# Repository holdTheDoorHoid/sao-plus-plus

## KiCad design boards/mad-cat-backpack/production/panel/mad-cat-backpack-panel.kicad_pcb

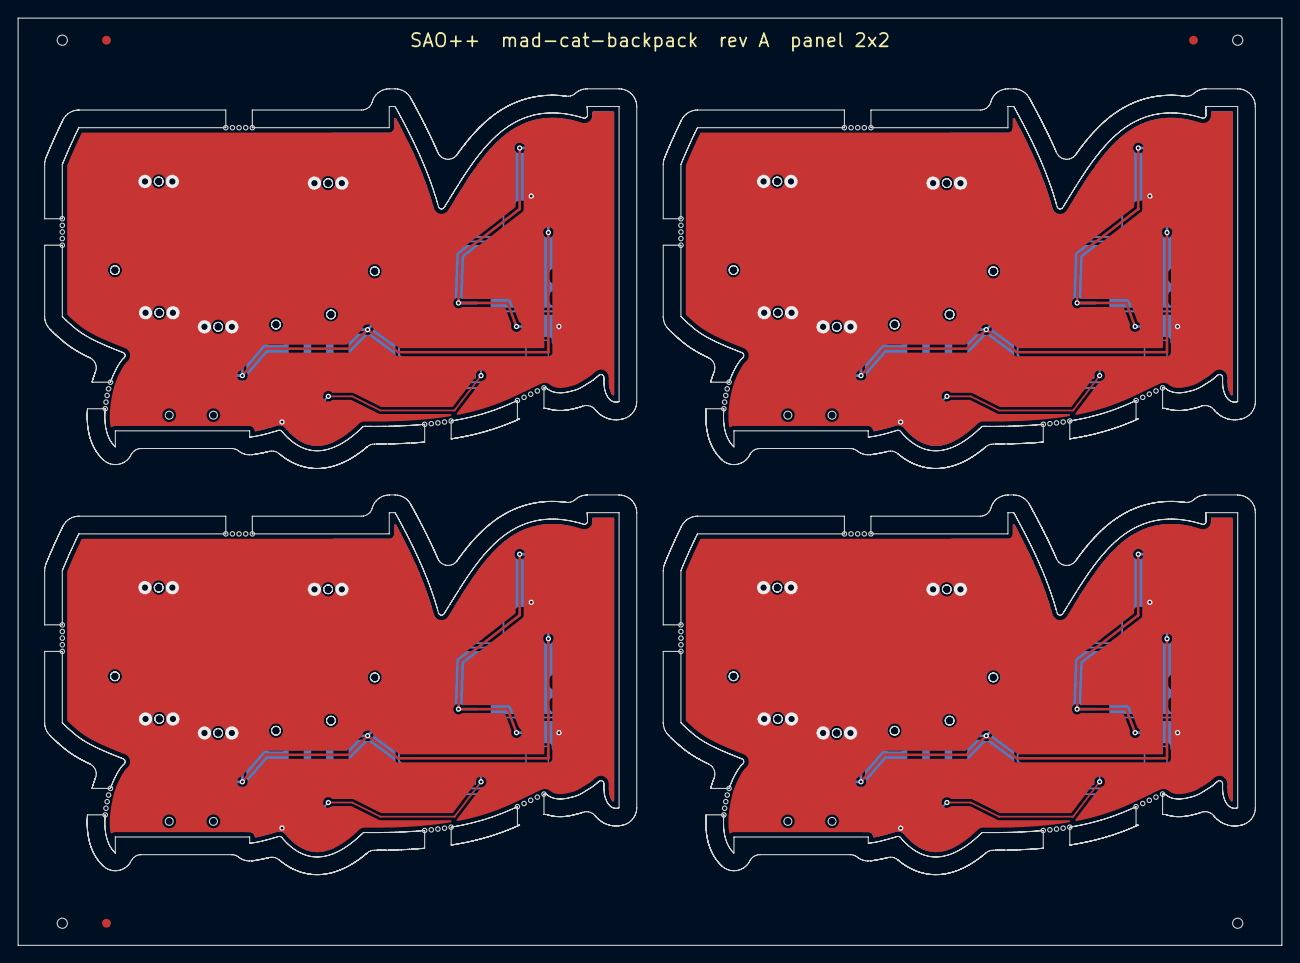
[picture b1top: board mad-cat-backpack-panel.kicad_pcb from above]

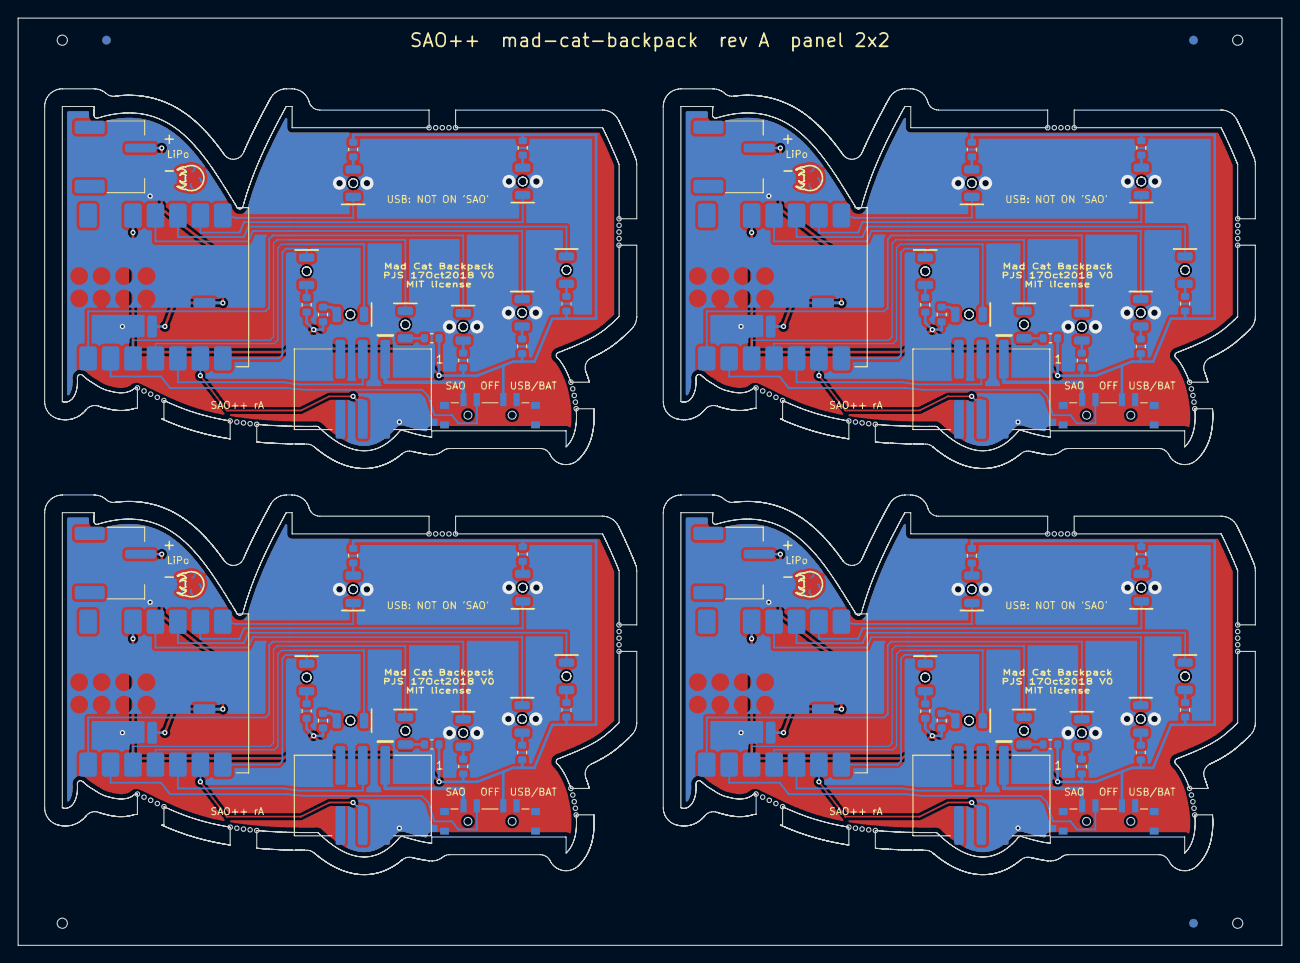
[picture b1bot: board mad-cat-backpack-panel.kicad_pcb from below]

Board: 2 copper layers, 143.0 x 104.9 mm, 80 parts (80 on the bottom side), 92 nets.

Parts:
D101, D102, D103, D104, D105, D106, D107, D108, D201, D202, D203, D204, D205, D206, D207, D208, D301, D302, D303, D304, D305, D306, D307, D308, D401, D402, D403, D404, D405, D406, D407, D408: white; SAOPP_LED-10_1206_ReverseMount_ThroughBoard
J101, J201, J301, J401: SAO v1.69bis; SAOPP_CONN-01_BoxHeader_2x03_P2.54mm_SMD_XFCN_BH254VS-6P
J102, J202, J302, J402: LiPo 3.7 V; SAOPP_CONN-10_JST_PH_S2B-PH-SM4-TB_1x02_Horizontal
R101, R102, R103, R104, R105, R106, R107, R108, R201, R202, R203, R204, R205, R206, R207, R208, R301, R302, R303, R304, R305, R306, R307, R308, R401, R402, R403, R404, R405, R406, R407, R408: 330; SAOPP_R_0603_1608Metric
SW101, SW201, SW301, SW401: SAO / OFF / BAT; SAOPP_SW-01_Slide_SP3T_CK_PCM13SMTR
U101, U201, U301, U401: XIAO ESP32-C3 / S3 / C6; SAOPP_MCU-01_Seeed_XIAO_SMD_C3_S3_C6

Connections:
B2-BAT+: J202.1, U201.15
B2-GND: J201.2, J202.2, U201.13, U201.16
B2-LED1_A: D201.2, R201.1
B2-LED1_K: D201.1, U201.9
B2-LED2_A: D202.2, R202.1
B2-LED2_K: D202.1, U201.8
B2-LED3_A: D203.2, R203.1
B2-LED3_K: D203.1, U201.10
B2-LED4_A: D204.2, R204.1
B2-LED4_K: D204.1, U201.11
B2-LED5_A: D205.2, R205.1
B2-LED5_K: D205.1, U201.1
B2-LED6_A: D206.2, R206.1
B2-LED6_K: D206.1, U201.3
B2-LED7_A: D207.2, R207.1
B2-LED7_K: D207.1, U201.4
B2-LED8_A: D208.2, R208.1
B2-LED8_K: D208.1, U201.7
B2-OFF_SENSE: SW201.2, U201.2
B2-SCL: J201.4, U201.6
B2-SDA: J201.3, U201.5
B2-V3V3: R201.2, R202.2, R203.2, R204.2, R205.2, R206.2, R207.2, R208.2, SW201.3, U201.12
B2-VSAO: J201.1, SW201.1
B3-BAT+: J302.1, U301.15
B3-GND: J301.2, J302.2, U301.13, U301.16
B3-LED1_A: D301.2, R301.1
B3-LED1_K: D301.1, U301.9
B3-LED2_A: D302.2, R302.1
B3-LED2_K: D302.1, U301.8
B3-LED3_A: D303.2, R303.1
B3-LED3_K: D303.1, U301.10
B3-LED4_A: D304.2, R304.1
B3-LED4_K: D304.1, U301.11
B3-LED5_A: D305.2, R305.1
B3-LED5_K: D305.1, U301.1
B3-LED6_A: D306.2, R306.1
B3-LED6_K: D306.1, U301.3
B3-LED7_A: D307.2, R307.1
B3-LED7_K: D307.1, U301.4
B3-LED8_A: D308.2, R308.1
B3-LED8_K: D308.1, U301.7
B3-OFF_SENSE: SW301.2, U301.2
B3-SCL: J301.4, U301.6
B3-SDA: J301.3, U301.5
B3-V3V3: R301.2, R302.2, R303.2, R304.2, R305.2, R306.2, R307.2, R308.2, SW301.3, U301.12
B3-VSAO: J301.1, SW301.1
B4-BAT+: J402.1, U401.15
B4-GND: J401.2, J402.2, U401.13, U401.16
B4-LED1_A: D401.2, R401.1
B4-LED1_K: D401.1, U401.9
B4-LED2_A: D402.2, R402.1
B4-LED2_K: D402.1, U401.8
B4-LED3_A: D403.2, R403.1
B4-LED3_K: D403.1, U401.10
B4-LED4_A: D404.2, R404.1
B4-LED4_K: D404.1, U401.11
B4-LED5_A: D405.2, R405.1
B4-LED5_K: D405.1, U401.1
B4-LED6_A: D406.2, R406.1
B4-LED6_K: D406.1, U401.3
B4-LED7_A: D407.2, R407.1
B4-LED7_K: D407.1, U401.4
B4-LED8_A: D408.2, R408.1
B4-LED8_K: D408.1, U401.7
B4-OFF_SENSE: SW401.2, U401.2
B4-SCL: J401.4, U401.6
B4-SDA: J401.3, U401.5
B4-V3V3: R401.2, R402.2, R403.2, R404.2, R405.2, R406.2, R407.2, R408.2, SW401.3, U401.12
B4-VSAO: J401.1, SW401.1
BAT+: J102.1, U101.15
GND: J101.2, J102.2, U101.13, U101.16
LED1_A: D101.2, R101.1
LED1_K: D101.1, U101.9
LED2_A: D102.2, R102.1
LED2_K: D102.1, U101.8
LED3_A: D103.2, R103.1
LED3_K: D103.1, U101.10
LED4_A: D104.2, R104.1
LED4_K: D104.1, U101.11
LED5_A: D105.2, R105.1
LED5_K: D105.1, U101.1
LED6_A: D106.2, R106.1
LED6_K: D106.1, U101.3
LED7_A: D107.2, R107.1
LED7_K: D107.1, U101.4
LED8_A: D108.2, R108.1
LED8_K: D108.1, U101.7
OFF_SENSE: SW101.2, U101.2
SCL: J101.4, U101.6
SDA: J101.3, U101.5
V3V3: R101.2, R102.2, R103.2, R104.2, R105.2, R106.2, R107.2, R108.2, SW101.3, U101.12
VSAO: J101.1, SW101.1

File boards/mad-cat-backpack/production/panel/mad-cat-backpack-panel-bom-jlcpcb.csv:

Comment,Designator,Footprint,LCSC Part #
white,"D101,D102,D103,D104,D105,D106,D107,D108,D201,D202,D203,D204,D205,D206,D207,D208,D301,D302,D303,D304,D305,D306,D307,D308,D401,D402,D403,D404,D405,D406,D407,D408",SAOPP_LED-10_1206_ReverseMount_ThroughBoard,C575513
SAO v1.69bis,"J101,J201,J301,J401",SAOPP_CONN-01_BoxHeader_2x03_P2.54mm_SMD_XFCN_BH254VS-6P,C492445
LiPo 3.7 V,"J102,J202,J302,J402",SAOPP_CONN-10_JST_PH_S2B-PH-SM4-TB_1x02_Horizontal,C295747
330,"R101,R102,R103,R104,R105,R106,R107,R108,R201,R202,R203,R204,R205,R206,R207,R208,R301,R302,R303,R304,R305,R306,R307,R308,R401,R402,R403,R404,R405,R406,R407,R408",SAOPP_R_0603_1608Metric,C23138
SAO / OFF / BAT,"SW101,SW201,SW301,SW401",SAOPP_SW-01_Slide_SP3T_CK_PCM13SMTR,C221842
XIAO ESP32-C3 / S3 / C6,"U101,U201,U301,U401",SAOPP_MCU-01_Seeed_XIAO_SMD_C3_S3_C6,

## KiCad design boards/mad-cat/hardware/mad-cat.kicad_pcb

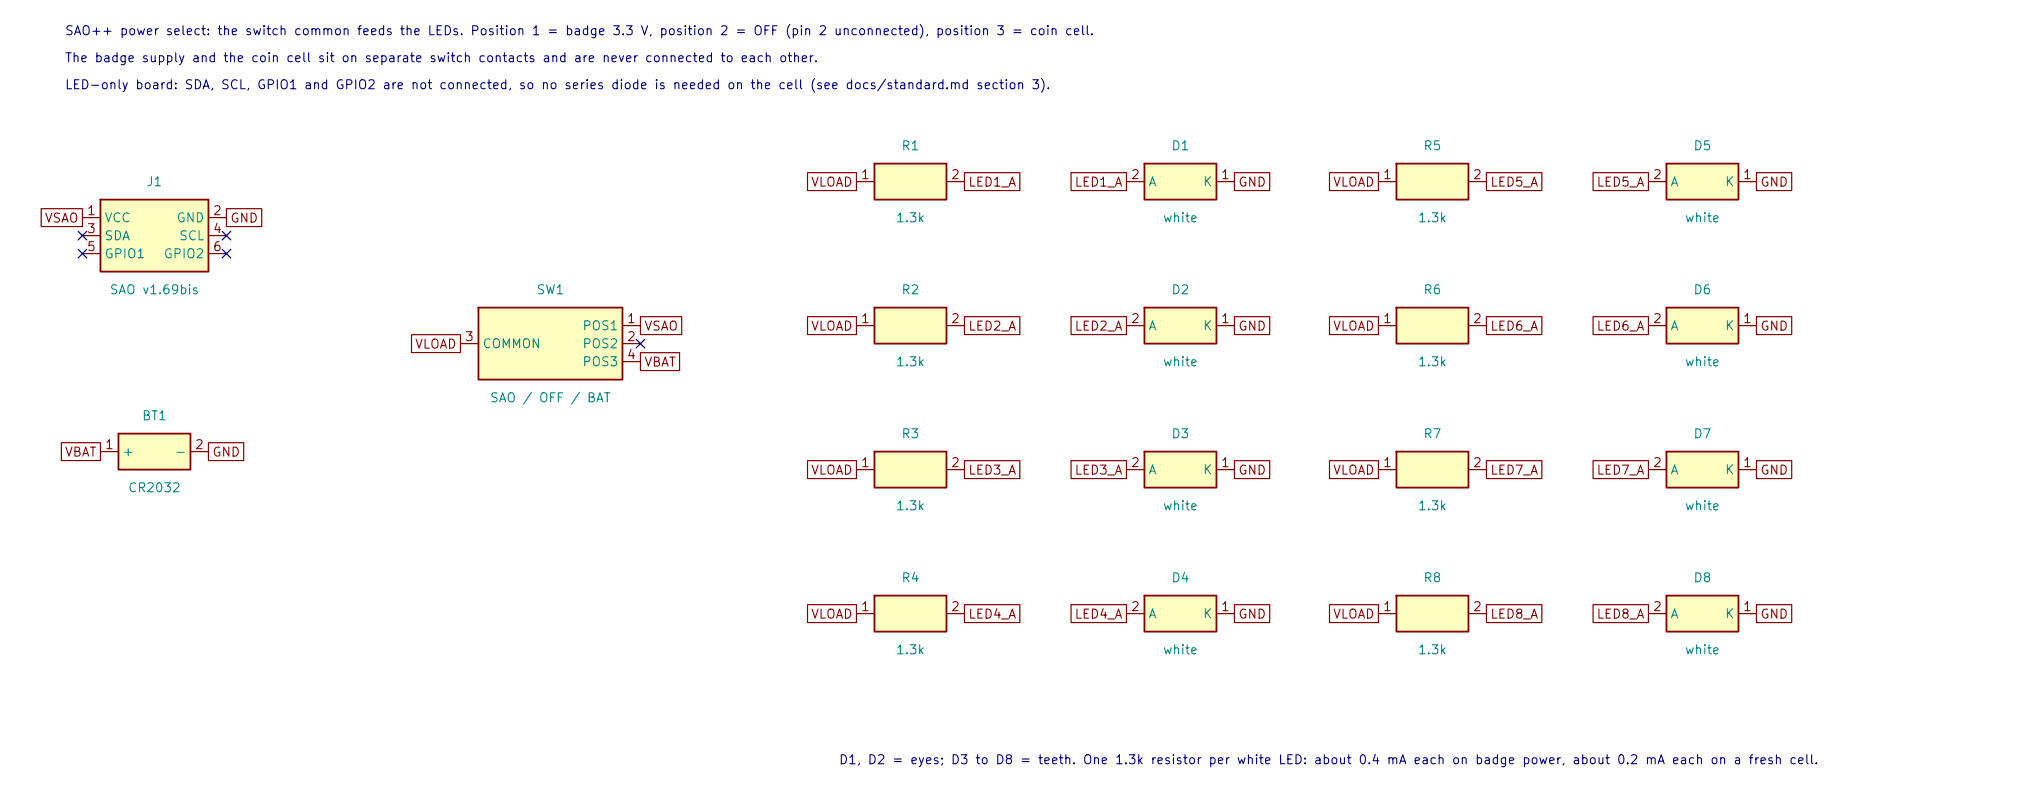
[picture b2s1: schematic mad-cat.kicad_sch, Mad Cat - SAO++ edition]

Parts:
BT1: CR2032; SAOPP_BAT-01_CR2032_SMD_TE_BAT-HLD-001; MPN BAT-HLD-001; LCSC C7501066
D1, D2, D3, D4, D5, D6, D7, D8: white; SAOPP_LED-10_1206_ReverseMount_ThroughBoard; MPN LTW-C230DS; LCSC C575513
J1: SAO v1.69bis; SAOPP_CONN-01_BoxHeader_2x03_P2.54mm_SMD_XFCN_BH254VS-6P; MPN BH254VS-6P; LCSC C492445
R1, R2, R3, R4, R5, R6, R7, R8: 1.3k; SAOPP_R_0603_1608Metric; MPN 0603WAF1301T5E; LCSC C22767
SW1: SAO / OFF / BAT; SAOPP_SW-01_Slide_SP3T_CK_PCM13SMTR; MPN PCM13SMTR; LCSC C221842

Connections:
GND: BT1.2 (-), D1.1 (K), D2.1 (K), D3.1 (K), D4.1 (K), D5.1 (K), D6.1 (K), D7.1 (K), D8.1 (K), J1.2 (GND)
LED1_A: D1.2 (A), R1.2
LED2_A: D2.2 (A), R2.2
LED3_A: D3.2 (A), R3.2
LED4_A: D4.2 (A), R4.2
LED5_A: D5.2 (A), R5.2
LED6_A: D6.2 (A), R6.2
LED7_A: D7.2 (A), R7.2
LED8_A: D8.2 (A), R8.2
VBAT: BT1.1 (+), SW1.4 (POS3)
VLOAD: R1.1, R2.1, R3.1, R4.1, R5.1, R6.1, R7.1, R8.1, SW1.3 (COMMON)
VSAO: J1.1 (VCC), SW1.1 (POS1)

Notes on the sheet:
SAO++ power select: the switch common feeds the LEDs. Position 1 = badge 3.3 V, position 2 = OFF (pin 2 unconnected), position 3 = coin cell.
The badge supply and the coin cell sit on separate switch contacts and are never connected to each other.
LED-only board: SDA, SCL, GPIO1 and GPIO2 are not connected, so no series diode is needed on the cell (see docs/standard.md section 3).
D1, D2 = eyes; D3 to D8 = teeth. One 1.3k resistor per white LED: about 0.4 mA each on badge power, about 0.2 mA each on a fresh cell.

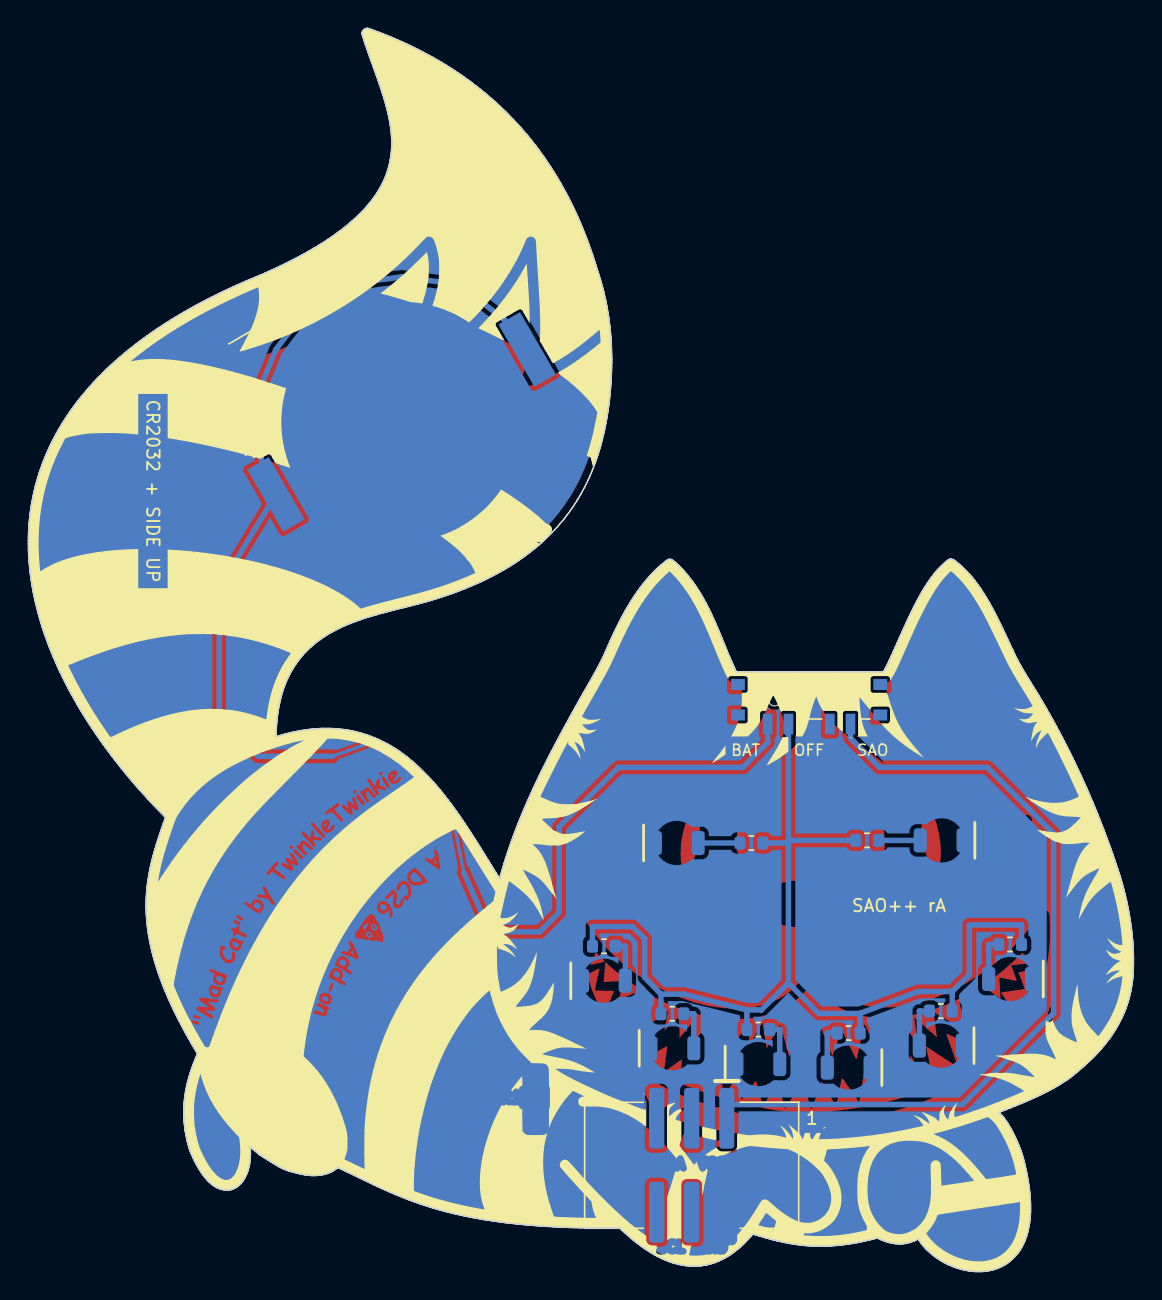
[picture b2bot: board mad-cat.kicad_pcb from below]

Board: 2 copper layers, 80.0 x 90.0 mm, 23 parts (19 on the bottom side), 12 nets.

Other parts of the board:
B.Cu: LOGO; B.Cu_g5726
B.Silk: LOGO; B.Silk_g5730
F.Cu: LOGO; F.Cu_g5732
F.Silk: LOGO; F.Silk_g5736

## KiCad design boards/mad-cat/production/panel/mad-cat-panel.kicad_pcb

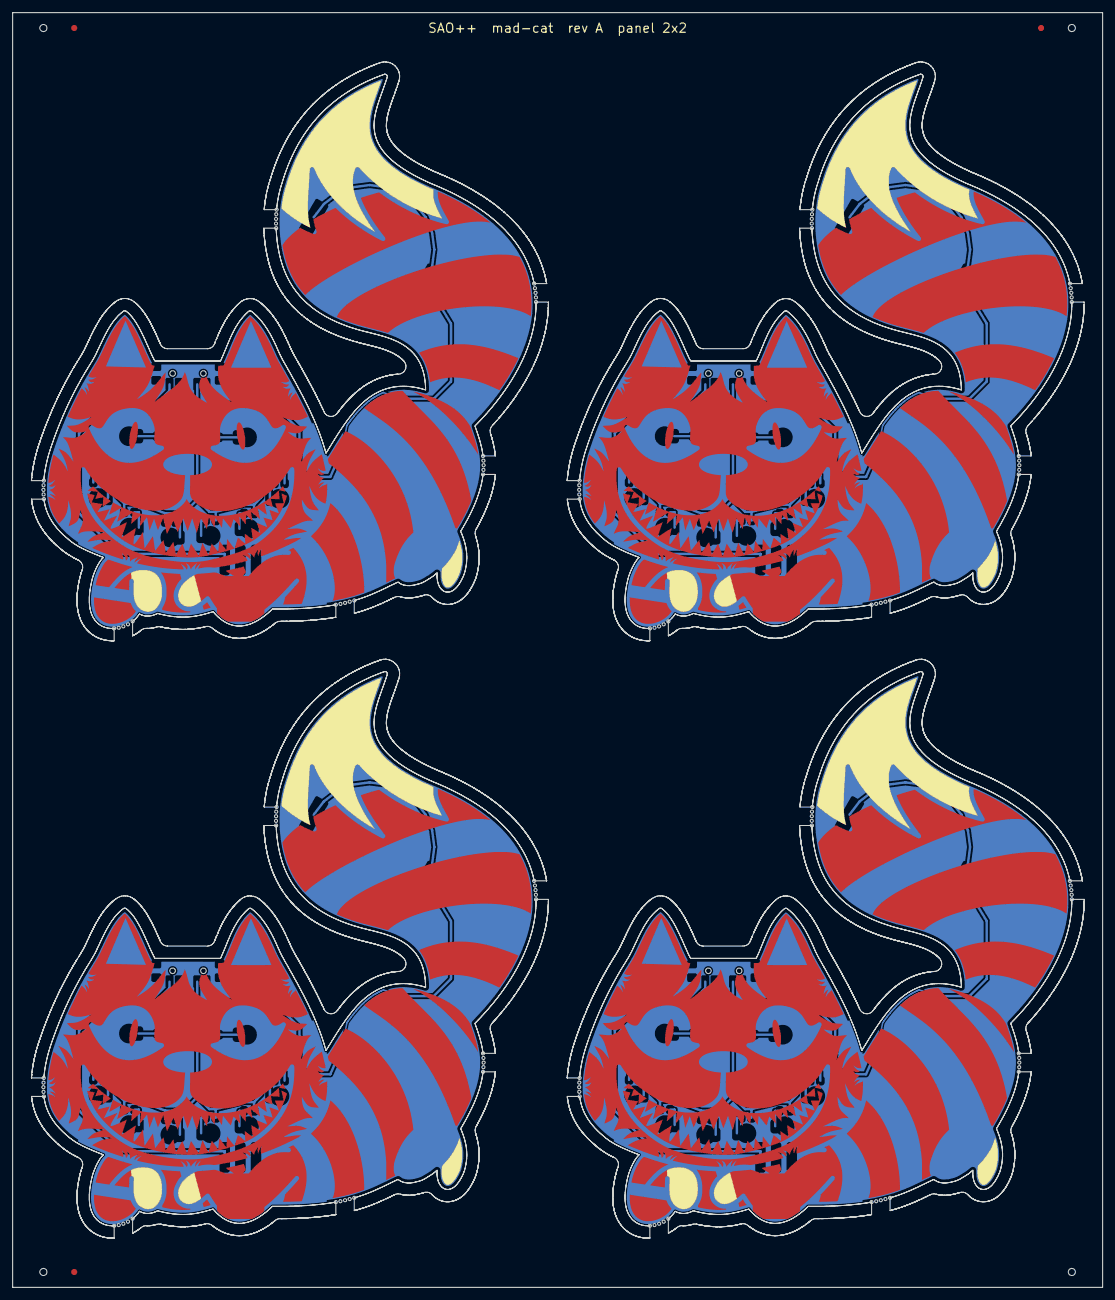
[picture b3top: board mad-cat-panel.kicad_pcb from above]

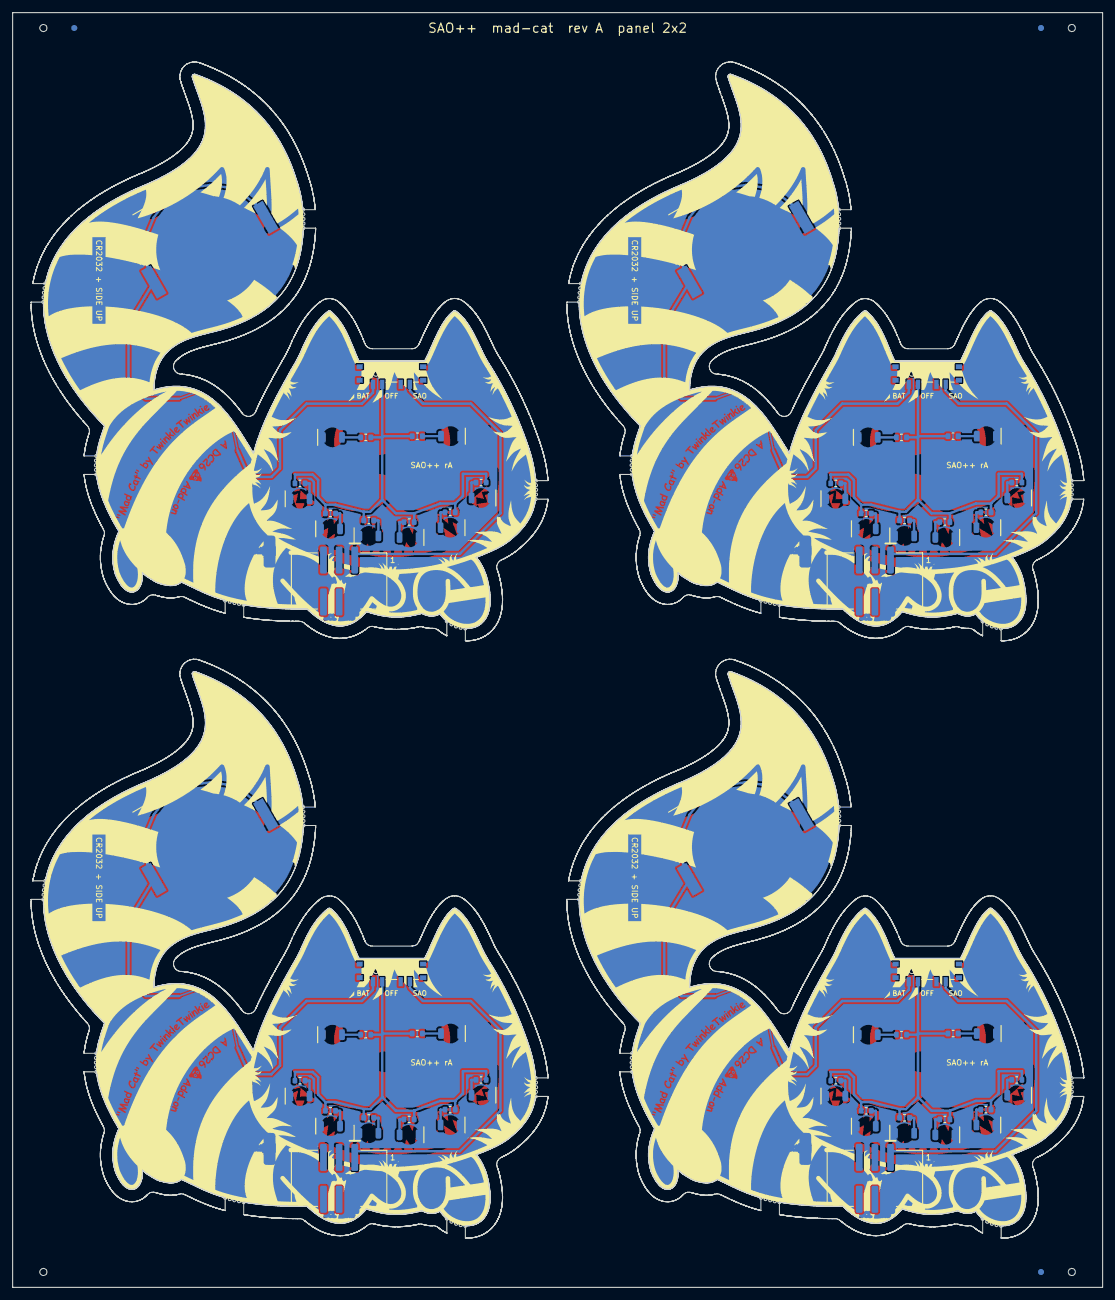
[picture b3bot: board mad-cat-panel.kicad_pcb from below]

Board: 2 copper layers, 177.0 x 207.0 mm, 92 parts (76 on the bottom side), 48 nets.

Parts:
B.Cu, B.Cu#2, B.Cu#3, B.Cu#4: LOGO; B.Cu_g5726
B.Silk, B.Silk#2, B.Silk#3, B.Silk#4: LOGO; B.Silk_g5730
BT101, BT201, BT301, BT401: CR2032; SAOPP_BAT-01_CR2032_SMD_TE_BAT-HLD-001
D101, D102, D103, D104, D105, D106, D107, D108, D201, D202, D203, D204, D205, D206, D207, D208, D301, D302, D303, D304, D305, D306, D307, D308, D401, D402, D403, D404, D405, D406, D407, D408: white; SAOPP_LED-10_1206_ReverseMount_ThroughBoard
F.Cu, F.Cu#2, F.Cu#3, F.Cu#4: LOGO; F.Cu_g5732
F.Silk, F.Silk#2, F.Silk#3, F.Silk#4: LOGO; F.Silk_g5736
J101, J201, J301, J401: SAO v1.69bis; SAOPP_CONN-01_BoxHeader_2x03_P2.54mm_SMD_XFCN_BH254VS-6P
R101, R102, R103, R104, R105, R106, R107, R108, R201, R202, R203, R204, R205, R206, R207, R208, R301, R302, R303, R304, R305, R306, R307, R308, R401, R402, R403, R404, R405, R406, R407, R408: 1.3k; SAOPP_R_0603_1608Metric
SW101, SW201, SW301, SW401: SAO / OFF / BAT; SAOPP_SW-01_Slide_SP3T_CK_PCM13SMTR

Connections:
B2-GND: BT201.2, D201.1, D202.1, D203.1, D204.1, D205.1, D206.1, D207.1, D208.1, J201.2
B2-LED1_A: D201.2, R201.2
B2-LED2_A: D202.2, R202.2
B2-LED3_A: D203.2, R203.2
B2-LED4_A: D204.2, R204.2
B2-LED5_A: D205.2, R205.2
B2-LED6_A: D206.2, R206.2
B2-LED7_A: D207.2, R207.2
B2-LED8_A: D208.2, R208.2
B2-VBAT: BT201.1, SW201.4
B2-VLOAD: R201.1, R202.1, R203.1, R204.1, R205.1, R206.1, R207.1, R208.1, SW201.3
B2-VSAO: J201.1, SW201.1
B3-GND: BT301.2, D301.1, D302.1, D303.1, D304.1, D305.1, D306.1, D307.1, D308.1, J301.2
B3-LED1_A: D301.2, R301.2
B3-LED2_A: D302.2, R302.2
B3-LED3_A: D303.2, R303.2
B3-LED4_A: D304.2, R304.2
B3-LED5_A: D305.2, R305.2
B3-LED6_A: D306.2, R306.2
B3-LED7_A: D307.2, R307.2
B3-LED8_A: D308.2, R308.2
B3-VBAT: BT301.1, SW301.4
B3-VLOAD: R301.1, R302.1, R303.1, R304.1, R305.1, R306.1, R307.1, R308.1, SW301.3
B3-VSAO: J301.1, SW301.1
B4-GND: BT401.2, D401.1, D402.1, D403.1, D404.1, D405.1, D406.1, D407.1, D408.1, J401.2
B4-LED1_A: D401.2, R401.2
B4-LED2_A: D402.2, R402.2
B4-LED3_A: D403.2, R403.2
B4-LED4_A: D404.2, R404.2
B4-LED5_A: D405.2, R405.2
B4-LED6_A: D406.2, R406.2
B4-LED7_A: D407.2, R407.2
B4-LED8_A: D408.2, R408.2
B4-VBAT: BT401.1, SW401.4
B4-VLOAD: R401.1, R402.1, R403.1, R404.1, R405.1, R406.1, R407.1, R408.1, SW401.3
B4-VSAO: J401.1, SW401.1
GND: BT101.2, D101.1, D102.1, D103.1, D104.1, D105.1, D106.1, D107.1, D108.1, J101.2
LED1_A: D101.2, R101.2
LED2_A: D102.2, R102.2
LED3_A: D103.2, R103.2
LED4_A: D104.2, R104.2
LED5_A: D105.2, R105.2
LED6_A: D106.2, R106.2
LED7_A: D107.2, R107.2
LED8_A: D108.2, R108.2
VBAT: BT101.1, SW101.4
VLOAD: R101.1, R102.1, R103.1, R104.1, R105.1, R106.1, R107.1, R108.1, SW101.3
VSAO: J101.1, SW101.1

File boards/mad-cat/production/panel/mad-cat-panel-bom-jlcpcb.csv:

Comment,Designator,Footprint,LCSC Part #
CR2032,"BT101,BT201,BT301,BT401",SAOPP_BAT-01_CR2032_SMD_TE_BAT-HLD-001,C7501066
white,"D101,D102,D103,D104,D105,D106,D107,D108,D201,D202,D203,D204,D205,D206,D207,D208,D301,D302,D303,D304,D305,D306,D307,D308,D401,D402,D403,D404,D405,D406,D407,D408",SAOPP_LED-10_1206_ReverseMount_ThroughBoard,C575513
SAO v1.69bis,"J101,J201,J301,J401",SAOPP_CONN-01_BoxHeader_2x03_P2.54mm_SMD_XFCN_BH254VS-6P,C492445
1.3k,"R101,R102,R103,R104,R105,R106,R107,R108,R201,R202,R203,R204,R205,R206,R207,R208,R301,R302,R303,R304,R305,R306,R307,R308,R401,R402,R403,R404,R405,R406,R407,R408",SAOPP_R_0603_1608Metric,C22767
SAO / OFF / BAT,"SW101,SW201,SW301,SW401",SAOPP_SW-01_Slide_SP3T_CK_PCM13SMTR,C221842

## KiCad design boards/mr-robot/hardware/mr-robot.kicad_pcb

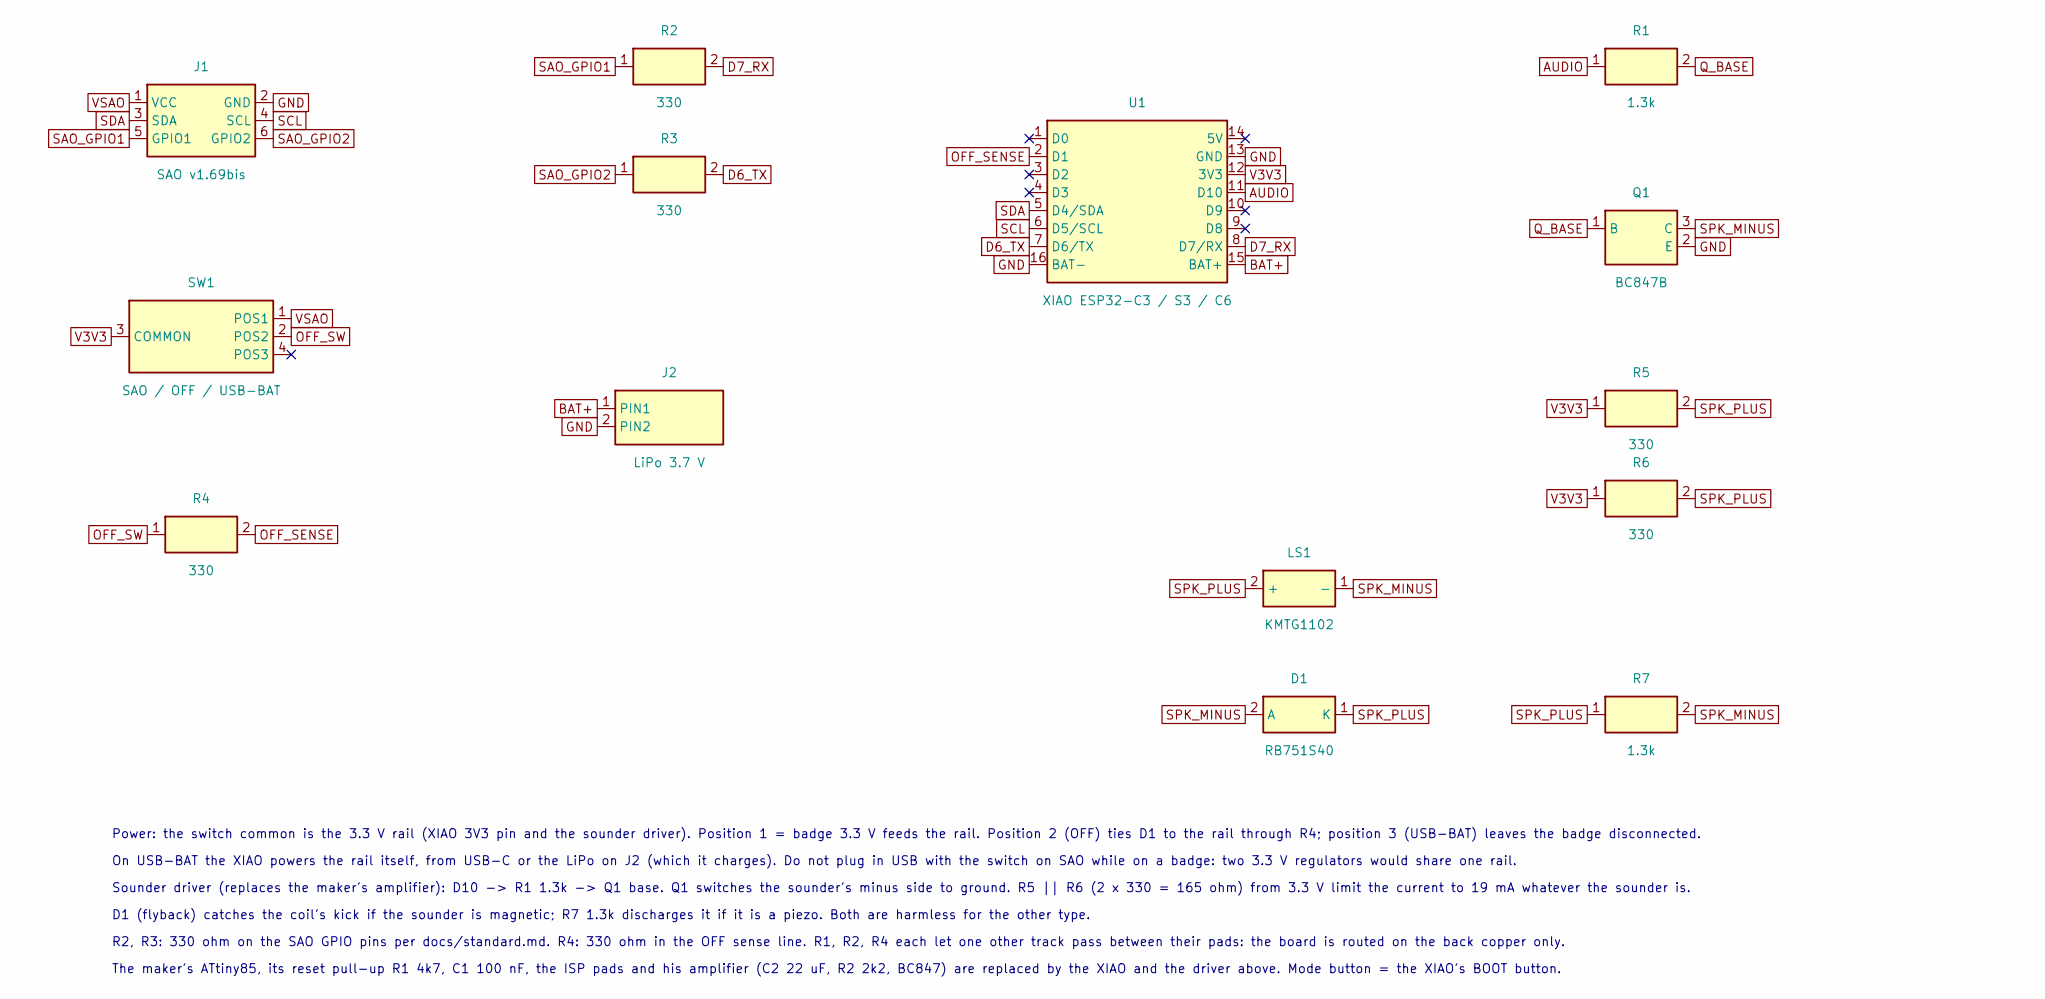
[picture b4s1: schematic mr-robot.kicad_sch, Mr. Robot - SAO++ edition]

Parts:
D1: RB751S40; D_SOD-523; MPN RB751S40T1G; LCSC C232576
J1: SAO v1.69bis; SAOPP_CONN-01_BoxHeader_2x03_P2.54mm_SMD_XFCN_BH254VS-6P; MPN BH254VS-6P; LCSC C492445
J2: LiPo 3.7 V; SAOPP_CONN-10_JST_PH_S2B-PH-SM4-TB_1x02_Horizontal; MPN S2B-PH-SM4-TB(LF)(SN); LCSC C295747
LS1: KMTG1102; KMTG-1102; MPN KMTG1102-A1
Q1: BC847B; SOT-23; MPN BC847B,215; LCSC C57668
R1, R7: 1.3k; SAOPP_R_0603_1608Metric; MPN 0603WAF1301T5E; LCSC C22767
R2, R3, R4, R5, R6: 330; SAOPP_R_0603_1608Metric; MPN 0603WAF3300T5E; LCSC C23138
SW1: SAO / OFF / USB-BAT; SAOPP_SW-01_Slide_SP3T_CK_PCM13SMTR; MPN PCM13SMTR; LCSC C221842
U1: XIAO ESP32-C3 / S3 / C6; SAOPP_MCU-01_Seeed_XIAO_SMD_C3_S3_C6; MPN XIAO ESP32-C3 / S3 / C6

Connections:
AUDIO: R1.1, U1.11 (D10)
BAT+: J2.1 (PIN1), U1.15 (BAT+)
D6_TX: R3.2, U1.7 (D6/TX)
D7_RX: R2.2, U1.8 (D7/RX)
GND: J1.2 (GND), J2.2 (PIN2), Q1.2 (E), U1.13 (GND), U1.16 (BAT-)
OFF_SENSE: R4.2, U1.2 (D1)
OFF_SW: R4.1, SW1.2 (POS2)
Q_BASE: Q1.1 (B), R1.2
SAO_GPIO1: J1.5 (GPIO1), R2.1
SAO_GPIO2: J1.6 (GPIO2), R3.1
SCL: J1.4 (SCL), U1.6 (D5/SCL)
SDA: J1.3 (SDA), U1.5 (D4/SDA)
SPK_MINUS: D1.2 (A), LS1.1 (-), Q1.3 (C), R7.2
SPK_PLUS: D1.1 (K), LS1.2 (+), R5.2, R6.2, R7.1
V3V3: R5.1, R6.1, SW1.3 (COMMON), U1.12 (3V3)
VSAO: J1.1 (VCC), SW1.1 (POS1)

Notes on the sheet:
Power: the switch common is the 3.3 V rail (XIAO 3V3 pin and the sounder driver). Position 1 = badge 3.3 V feeds the rail. Position 2 (OFF) ties D1 to the rail through R4; position 3 (USB-BAT) leaves the badge disconnected.
On USB-BAT the XIAO powers the rail itself, from USB-C or the LiPo on J2 (which it charges). Do not plug in USB with the switch on SAO while on a badge: two 3.3 V regulators would share one rail.
Sounder driver (replaces the maker's amplifier): D10 -> R1 1.3k -> Q1 base. Q1 switches the sounder's minus side to ground. R5 || R6 (2 x 330 = 165 ohm) from 3.3 V limit the current to 19 mA whatever the sounder is.
D1 (flyback) catches the coil's kick if the sounder is magnetic; R7 1.3k discharges it if it is a piezo. Both are harmless for the other type.
R2, R3: 330 ohm on the SAO GPIO pins per docs/standard.md. R4: 330 ohm in the OFF sense line. R1, R2, R4 each let one other track pass between their pads: the board is routed on the back copper only.
The maker's ATtiny85, its reset pull-up R1 4k7, C1 100 nF, the ISP pads and his amplifier (C2 22 uF, R2 2k2, BC847) are replaced by the XIAO and the driver above. Mode button = the XIAO's BOOT button.

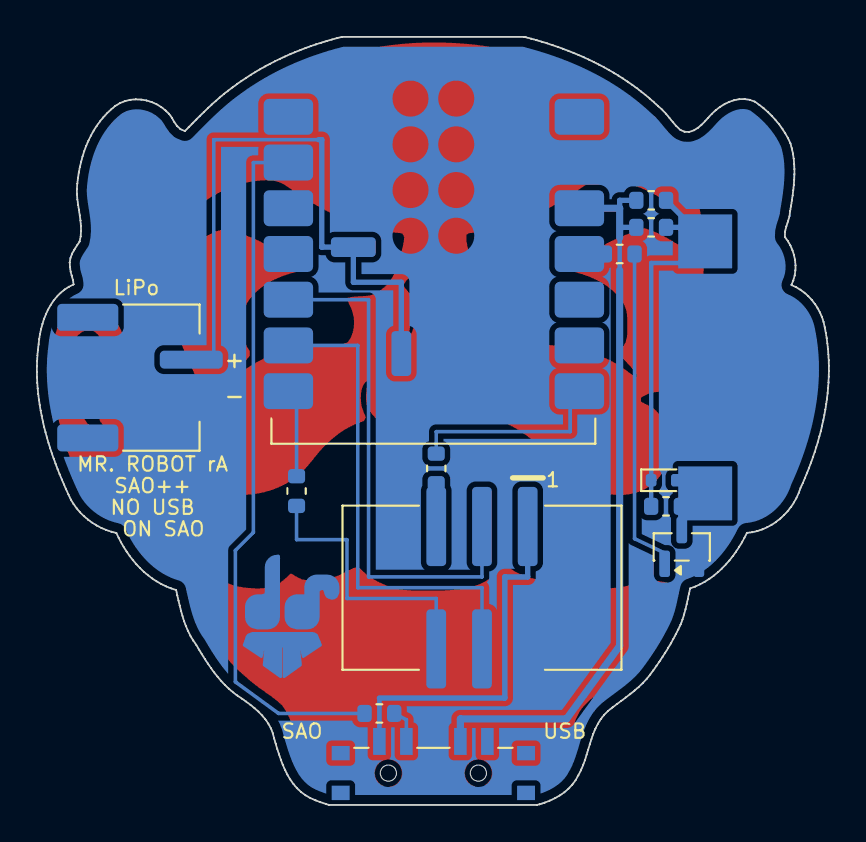
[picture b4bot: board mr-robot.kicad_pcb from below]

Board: 2 copper layers, 44.0 x 42.7 mm, 14 parts (14 on the bottom side), 16 nets.

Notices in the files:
boards/mad-cat-backpack/production/panel/mad-cat-backpack-panel.kicad_pcb:
Original design: Peter Shabino (Wireb), 2018, github.com/Wireb/Mad_Cat_Backpack, MIT license
MIT license
